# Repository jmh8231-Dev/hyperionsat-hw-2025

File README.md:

# HyperionSAT Flight‑Computer – 하드웨어 (2025)

> **Rev**: 1.0 · **ECAD**: KiCad 9.0.4 · **MCU**: STM32H723VGT6 (550 MHz, DP‑FPU)  
> **역할**: 2차 추진, TVC 제어, 센싱, 통신을 담당하는 하이브리드 비행 컴퓨터

---

<h3>3D Rendering</h3>
<table>
  <tr>
    <td></td>
    <td></td>
  </tr>
  <tr>
    <td align="center"><sub>Top</sub></td>
    <td align="center"><sub>Bottom</sub></td>
  </tr>

  <tr>
    <td></td>
    <td></td>
  </tr>
  <tr>
    <td align="center"><sub>SUB Top</sub></td>
    <td align="center"><sub>SUB Bottom</sub></td>
  </tr>
</table>

---

## 리포지토리 구성 (스냅샷)
```
docs/
└─ images/
   ├─ sch_processor.png
   ├─ sch_sensors.png
   ├─ sch_pmic.png
   ├─ sch_comm.png
   ├─ sch_actuators.png
   └─ sch_additional.png
README.md
```

---

## 1) 시스템 개요

**블록**
- **Processor**: STM32H723VGT6, 12 MHz TCXO, SWD, EEPROM(AT24C08C), RTC(DS3231M), Buzzer/LED, microSD(SDMMC 4‑bit).
- **Flight Sensors**: ICM‑45686(SPI), ICM‑20948(SPI, 1.8 V IO), MS5611(SPI), MMC5983MA(SPI), MAX‑M10S(UART+PPS), VL53L1X(I²C), **CDS‑Top/Bottom**(Bottom=TLV9001 버퍼).
- **Actuators**: TVC 서보 X/Y(12 V), **리니어 솔레노이드**(IRF1404, 어댑터 분리), **낙하산 전개 전자석**(DRV8871DDA).
- **Communications**: LoRa E32‑433T37S(UART + M0/M1/AUX), **Globalstar STX‑3**(UART + EN/RESET), RF 매칭 네트워크.
- **PMIC/Power**: 메인 Li‑Po 3S(셀1/2 버퍼드 ADC), **점화 배터리**(팩 전압 ADC), 3.3 V 스위칭, **INA219** 방전/점화 전류 측정, **AS6221** 온도.

**점화(IGN)**: **1채널** 구성으로 단순화됨.

<h3>Block Diagrams</h3>
<table>
  <tr>
    <td></td>
    <td></td>
    <td></td>
  </tr>
  <tr>
    <td align="center"><sub>OBC</sub></td>
    <td align="center"><sub>Communication</sub></td>
    <td align="center"><sub>Power</sub></td>
  </tr>
</table>

---

## 2) 전기적 인터페이스 (네트 라벨 기준)

### SPI
| Bus | Device | Signals |
|---|---|---|
| SPI‑A | ICM‑45686 | `ICM-45686_SCK/MISO/MOSI/CS`, `ICM-45686_INT` |
| SPI‑B | ICM‑20948, MS5611 | `ICM-20948_SCK/MISO/MOSI/CS`, `IMU2_INT`; `Barometer_SCK/MISO/MOSI/CS` |
| SPI‑C | MMC5983MA | `MMC5983MA_SCK/MISO/MOSI/CS`, `MMC5983MA_INT` |

### I²C (7‑bit)
| Bus | Device | Addr |
|---|---|---|
| RTC | DS3231M | 0x68 |
| EEPROM | AT24C08C | 0x50 *(데이터시트 8‑bit 코드 0xA0)* |
| TEMP | AS6221(Board/PMIC/FET/LoRa) | 0x48 / 0x49 / 0x4B / 0x4A |
| IGN | INA219 | 0x41 |

### UART / 타이밍 / GPIO
| Link | Signals |
|---|---|
| Debug | `Debug_Tx`, `Debug_Rx` |
| LoRa(E32) | `RF_Tx`, `RF_Rx`, `RF_M0`, `RF_M1`, `RF_AUX` |
| STX‑3 | `STX-3_Tx`, `STX-3_Rx`, `STX-3_CTS`, `STX-3_RTS`, `STX-3_EN`, `STX-3_Reset` |
| GPS | `GPS_Tx`, `GPS_Rx`, `GPS_PPS` |
| SDMMC | `SDMMC_D0..D3`, `SDMMC_CLK`, `SDMMC_CMD`, `SDMMC_DET`, `SDMMC_WP` |
| Actuators | `Servo_X`, `Servo_Y`, `Solenoid_Gate`, `DRV8871_A`, `DRV8871_B` |
| Analog | `Main_Cell1_ADC`, `Main_Cell2_ADC`, `IGN_BAT_ADC`, `Back-up_BAT_ADC`, `CDS_Top`, `CDS_Bottom_ADC` |

---

## 3) 회로도 스냅샷

- **Processor**  

- **Flight Sensors**  

- **PMIC / Power**  

- **Communications**  

- **Actuators**  

- **Additional parts (Magnetometer SPI, CDS Bottom 버퍼, LoRa 온도)**  

> **Firmware repo**: [https://github.com/ORG/REPO-FW  ](https://github.com/jmh8231-Dev/hyperionsat-fw-2025)

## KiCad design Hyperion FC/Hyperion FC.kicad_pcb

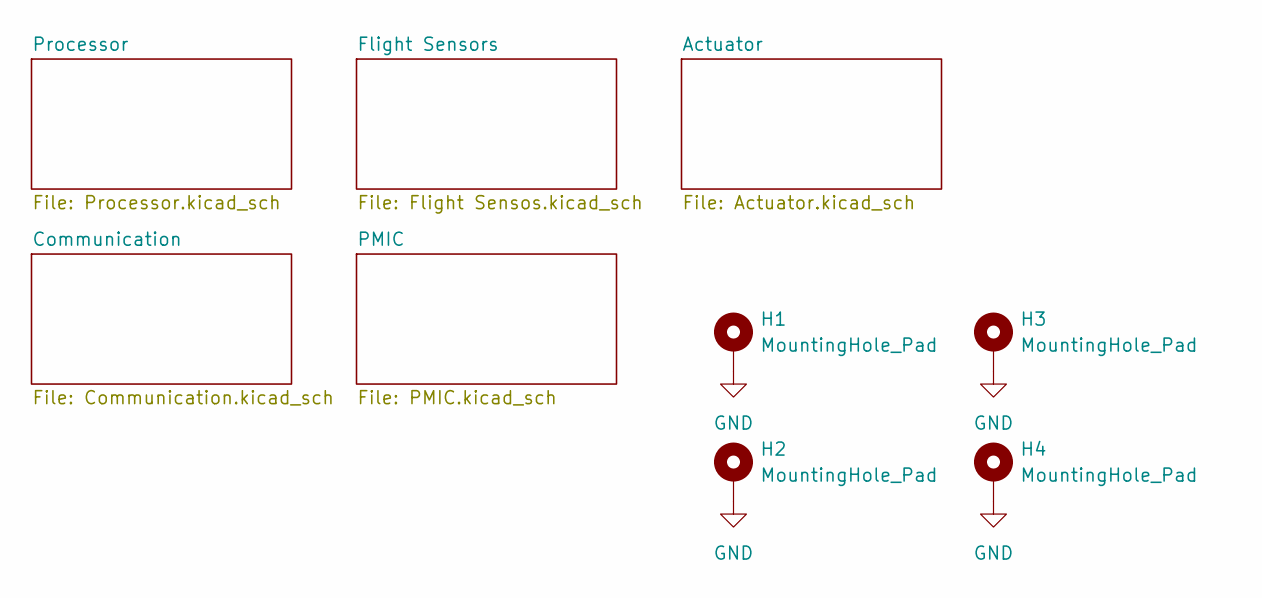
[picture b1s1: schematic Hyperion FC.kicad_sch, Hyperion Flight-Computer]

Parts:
H1, H2, H3, H4: MountingHole_Pad; MountingHole_2.7mm_M2.5_Pad_Via

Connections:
GND: H1.1, H2.1, H3.1, H4.1; also elsewhere on the board

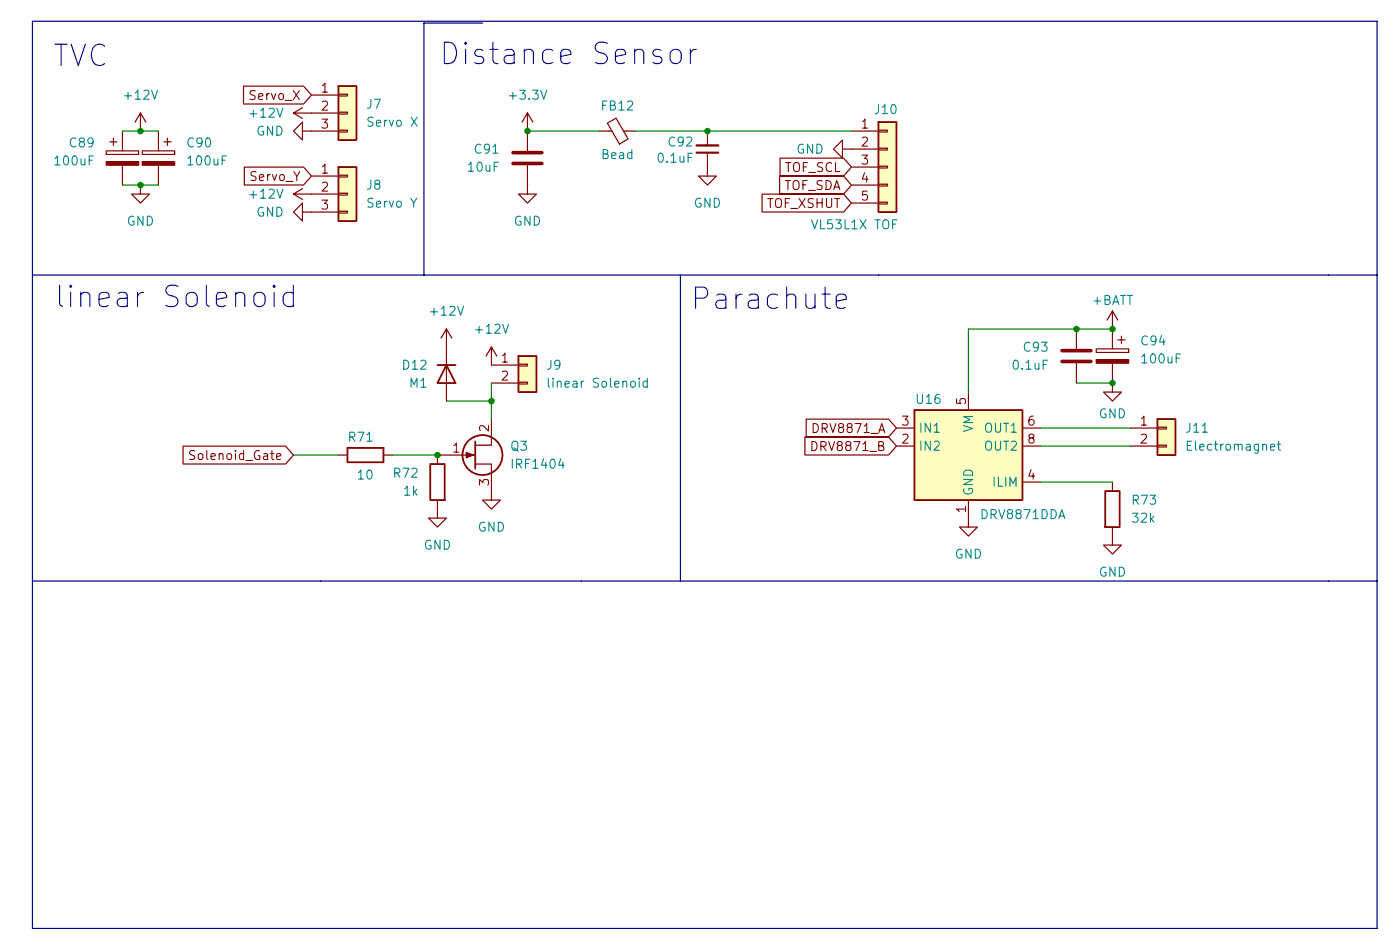
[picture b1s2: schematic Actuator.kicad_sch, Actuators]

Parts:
C89, C90, C94: 100uF; CP_EIA-7343-43_Kemet-X
C91: 10uF; C_0805_2012Metric
C92, C93: 0.1uF; C_0603_1608Metric
D12: M1; D_SMA
FB12: Bead; L_0603_1608Metric
J7: Servo X; JST_VH_B3P-VH_1x03_P3.96mm_Vertical
J8: Servo Y; JST_VH_B3P-VH_1x03_P3.96mm_Vertical
J9: linear Solenoid; JST_VH_B2P-VH_1x02_P3.96mm_Vertical
J10: VL53L1X TOF; SAMTEC_T1M-05-F-SH-L
J11: Electromagnet; JST_VH_B2P-VH_1x02_P3.96mm_Vertical
Q3: IRF1404; TO-263-2
R71: 10; R_0603_1608Metric
R72: 1k; R_0603_1608Metric
R73: 32k; R_0603_1608Metric
U16: DRV8871DDA; Texas_HTSOP-8-1EP_3.9x4.9mm_P1.27mm_EP2.95x4.9mm_Mask2.4x3.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

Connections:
+3.3V: C91.1, FB12.2; also elsewhere on the board
+12V: C89.1, C90.1, D12.1 (K), J7.2, J8.2, J9.1; also elsewhere on the board
+BATT: C93.1, C94.1, U16.5 (VM); also elsewhere on the board
DRV8871_A: U16.3 (IN1); also elsewhere on the board
DRV8871_B: U16.2 (IN2); also elsewhere on the board
GND: C89.2, C90.2, C91.2, C92.1, C93.2, C94.2, J7.3, J8.3, J10.2, Q3.3 (S), R72.2, R73.2, U16.1 (GND), U16.7 (GND), U16.9 (GND); also elsewhere on the board
I2C4_SCL: J10.3; also elsewhere on the board
I2C4_SDA: J10.4; also elsewhere on the board
unnamed: D12.2 (A), J9.2, Q3.2 (D)
unnamed: C92.2, FB12.1, J10.1
unnamed: J11.1, U16.6 (OUT1)
unnamed: J11.2, U16.8 (OUT2)
unnamed: Q3.1 (G), R71.2, R72.1
unnamed: R73.1, U16.4 (ILIM)
Servo_X: J7.1; also elsewhere on the board
Servo_Y: J8.1; also elsewhere on the board
Solenoid_Gate: R71.1; also elsewhere on the board
TOF_XSHUT: J10.5; also elsewhere on the board

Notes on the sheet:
linear Solenoid
Parachute
TVC
Distance Sensor

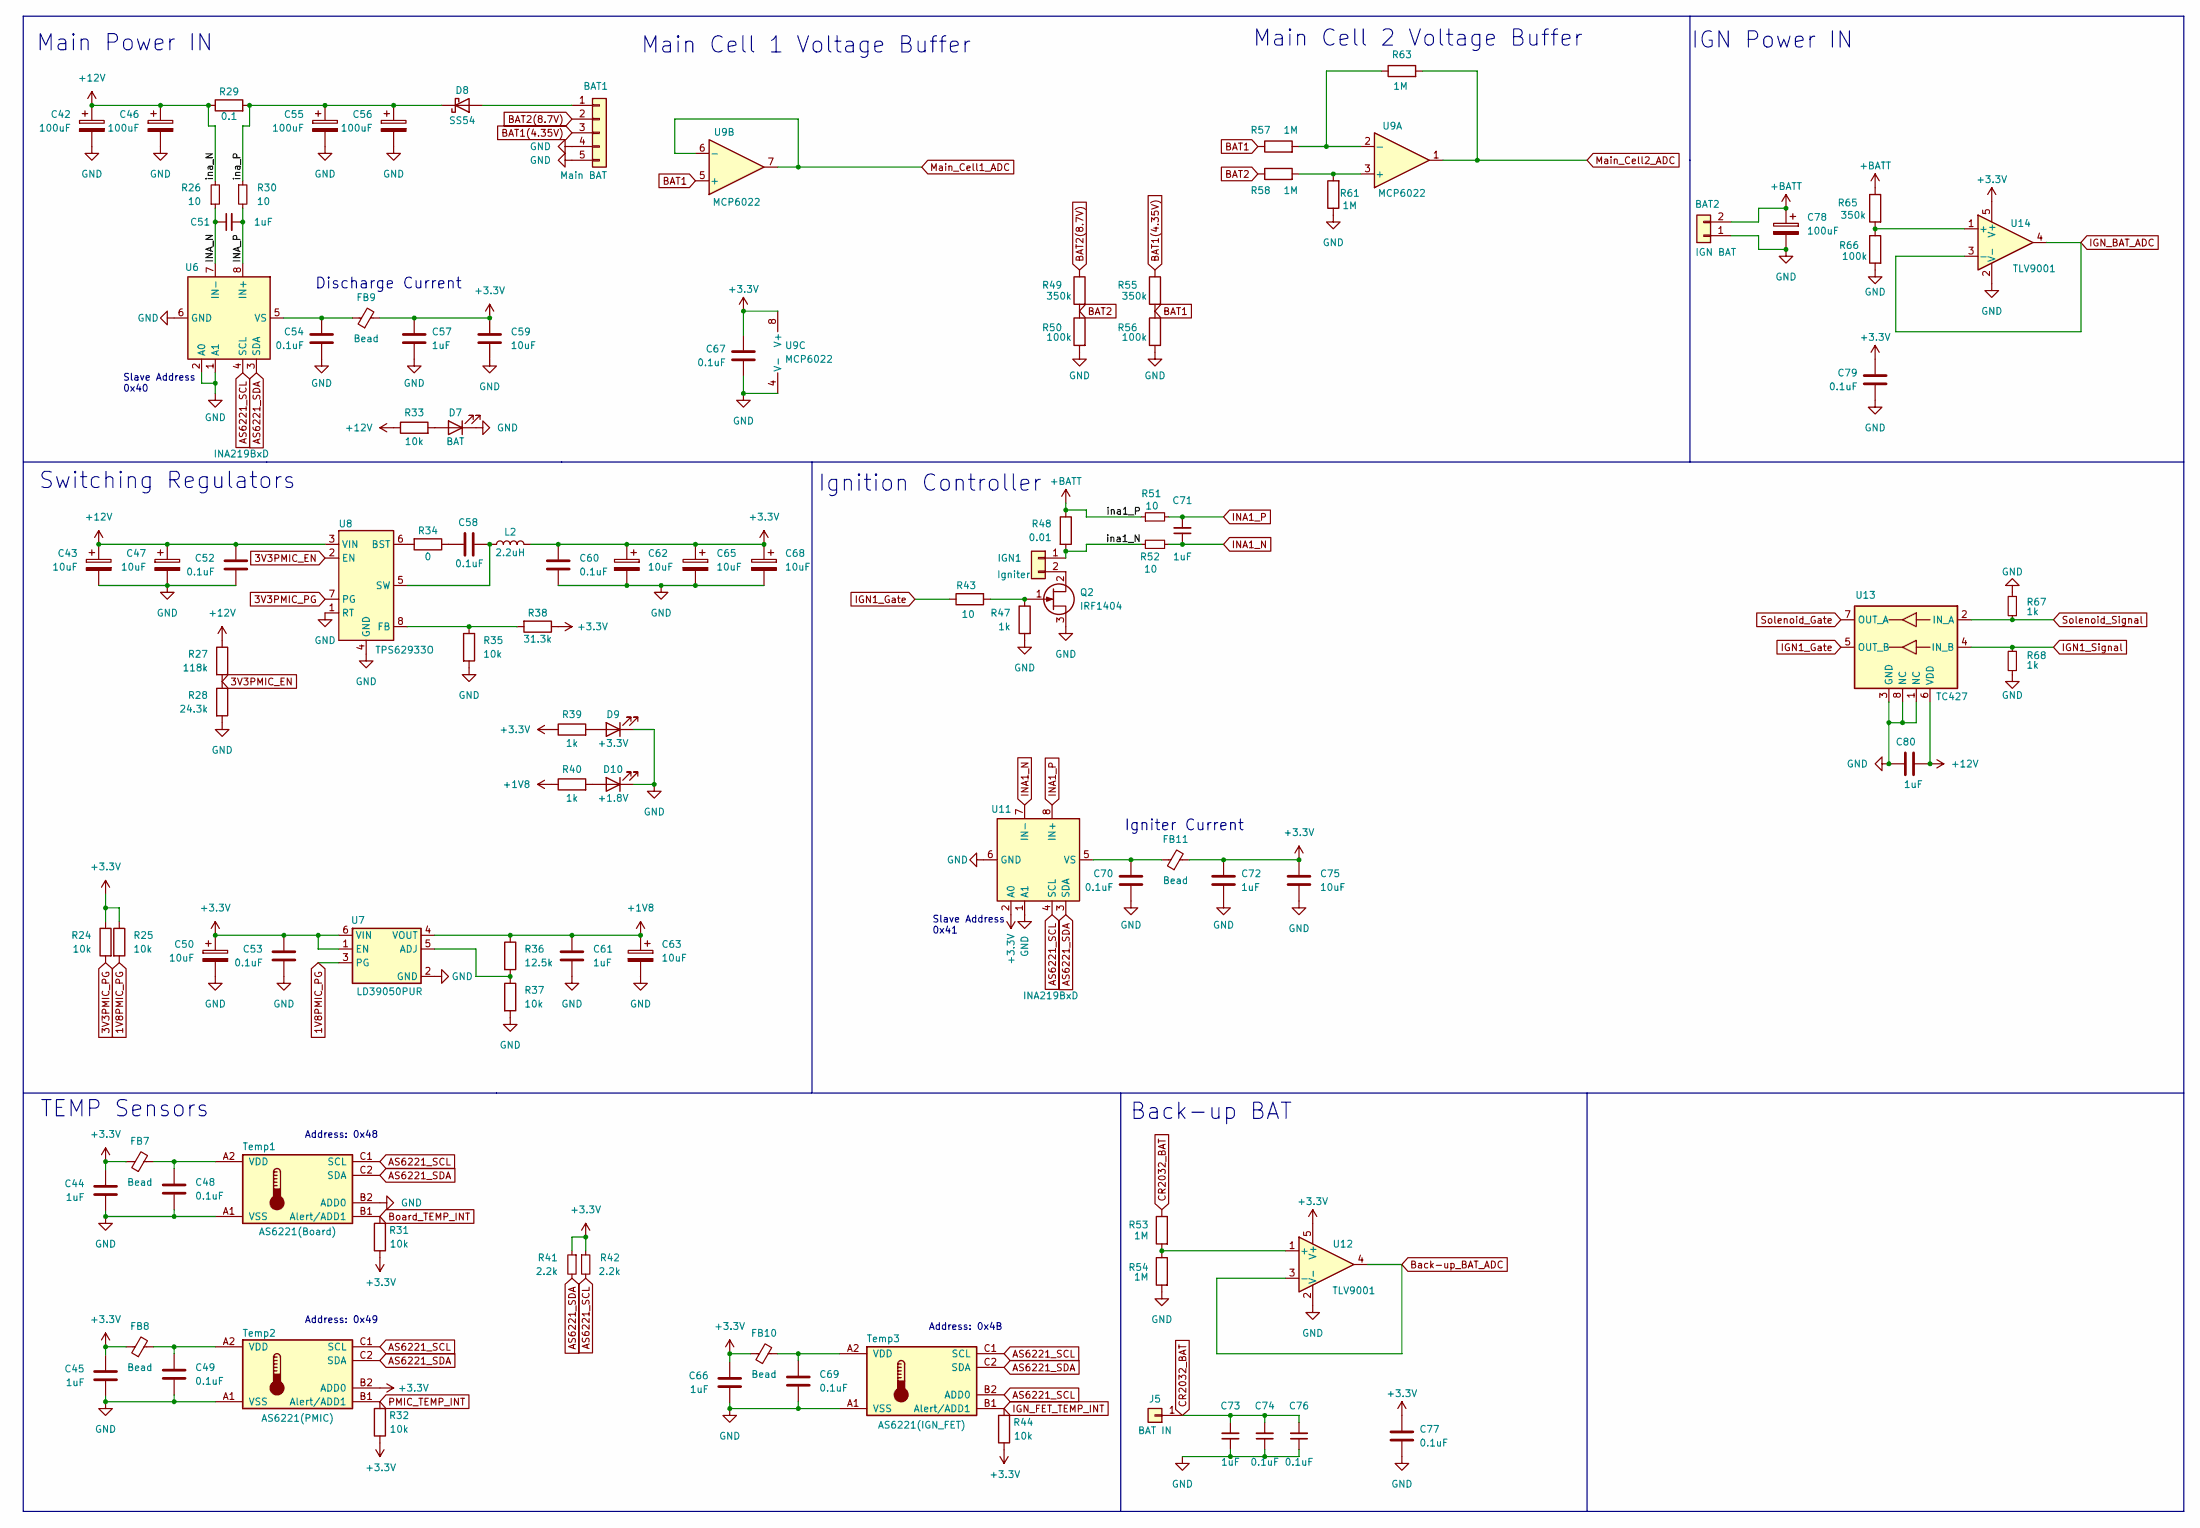
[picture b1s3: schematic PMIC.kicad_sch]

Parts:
BAT1: Main BAT; SAMTEC_T1M-05-F-SH-L
BAT2: IGN BAT; AMASS_XT30U-M_1x02_P5.0mm_Vertical
C42, C46, C55, C56, C78: 100uF; CP_EIA-7343-43_Kemet-X
C43, C47, C50, C59, C62, C63, C65, C68, C75: 10uF; C_0805_2012Metric
C44, C45, C51, C57, C61, C66, C71, C72, C73, C80: 1uF; C_0603_1608Metric
C48, C49, C52, C53, C54, C58, C60, C67, C69, C70, C74, C76, C77, C79: 0.1uF; C_0603_1608Metric
D7: BAT; LED_0805_2012Metric
D8: SS54; D_SMA
D9: +3.3V; LED_0805_2012Metric
D10: +1.8V; LED_0805_2012Metric
FB7, FB8, FB9, FB10, FB11: Bead; L_0603_1608Metric
IGN1: Igniter; JST_VH_B2P-VH_1x02_P3.96mm_Vertical
J5: BAT IN; PinHeader_1x01_P2.54mm_Vertical
L2: 2.2uH; L_Coilcraft_XAL6030-XXX
Q2: IRF1404; TO-263-2
R24, R25, R31, R32, R33, R35, R37, R44: 10k; R_0603_1608Metric
R26, R30, R43, R51, R52: 10; R_0603_1608Metric
R27: 118k; R_0603_1608Metric
R28: 24.3k; R_0603_1608Metric
R29: 0.1; R_2816_7142Metric
R34: 0; R_0603_1608Metric
R36: 12.5k; R_0603_1608Metric
R38: 31.3k; R_0603_1608Metric
R39, R40, R47, R67, R68: 1k; R_0603_1608Metric
R41, R42: 2.2k; R_0603_1608Metric
R48: 0.01; R_2816_7142Metric
R49, R55, R65: 350k; R_0603_1608Metric
R50, R56, R66: 100k; R_0603_1608Metric
R53, R54, R57, R58, R61, R63: 1M; R_0603_1608Metric
Temp1: AS6221(Board); WLCSP-6_1.4x1.0mm_P0.4mm
Temp2: AS6221(PMIC); WLCSP-6_1.4x1.0mm_P0.4mm
Temp3: AS6221(IGN_FET); WLCSP-6_1.4x1.0mm_P0.4mm
U6, U11: INA219BxD; SOIC-8_3.9x4.9mm_P1.27mm
U7: LD39050PUR; DFN-6-1EP_3x3mm_P0.95mm_EP1.7x2.6mm
U8: TPS62933O; SOT-583-8
U9: MCP6022; SOIC-8_3.9x4.9mm_P1.27mm
U12, U14: TLV9001; SOT-353_SC-70-5
U13: TC427; SOIC-8_3.9x4.9mm_P1.27mm

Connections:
1V8PMIC_PG: R25.2, U7.3 (PG); also elsewhere on the board
3V3PMIC_EN: R27.2, R28.1, U8.2 (EN)
3V3PMIC_PG: R24.2, U8.7 (PG); also elsewhere on the board
+1V8: C61.1, C63.1, R36.1, R40.1, U7.4 (VOUT); also elsewhere on the board
+3.3V: C44.2, C45.2, C50.1, C53.1, C57.1, C59.1, C60.1, C62.1, C65.1, C66.2, C67.2, C68.1, C72.1, C75.1, C77.2, C79.2, FB7.1, FB8.1, FB9.2, FB10.1, FB11.2, L2.2, R24.1, R25.1, R31.1, R32.1, R38.1, R39.1, R41.1, R42.1, R44.1, Temp2.B2 (ADD0), U7.1 (EN), U7.6 (VIN), U9.8 (V+), U11.2 (A0), U12.5 (V+), U14.5 (V+); also elsewhere on the board
+12V: C42.1, C43.1, C46.1, C47.1, C52.1, C80.2, R26.2, R27.1, R29.1, R33.1, U8.3 (VIN), U13.6 (VDD); also elsewhere on the board
+BATT: BAT2.2, C78.1, R48.1, R51.1, R65.1; also elsewhere on the board
/PMIC/INA_N: C51.1, R26.1, U6.7 (IN-)
/PMIC/INA_P: C51.2, R30.2, U6.8 (IN+)
/PMIC/ina1_N: IGN1.1, R48.2, R52.2
/PMIC/ina_P: C55.1, C56.1, D8.1 (K), R29.2, R30.1
AS6221_SCL: R42.2, Temp1.C1 (SCL), Temp2.C1 (SCL), Temp3.B2 (ADD0), Temp3.C1 (SCL), U6.4 (SCL), U11.4 (SCL); also elsewhere on the board
AS6221_SDA: R41.2, Temp1.C2 (SDA), Temp2.C2 (SDA), Temp3.C2 (SDA), U6.3 (SDA), U11.3 (SDA); also elsewhere on the board
BAT1: R55.2, R56.1, R57.1, U9.5 (+)
BAT1(4.35V): BAT1.3, R55.1
BAT2: R49.2, R50.1, R58.1
BAT2(8.7V): BAT1.2, R49.1
Back-up_BAT_ADC: U12.3 (-), U12.4; also elsewhere on the board
Board_TEMP_INT: R31.2, Temp1.B1 (Alert/ADD1); also elsewhere on the board
CR2032_BAT: C73.2, C74.2, C76.2, J5.1, R53.1; also elsewhere on the board
GND: BAT1.4, BAT1.5, BAT2.1, C42.2, C43.2, C44.1, C45.1, C46.2, C47.2, C48.2, C49.2, C50.2, C52.2, C53.2, C54.2, C55.2, C56.2, C57.2, C59.2, C60.2, C61.2, C62.2, C63.2, C65.2, C66.1, C67.1, C68.2, C69.2, C70.2, C72.2, C73.1, C74.1, C75.2, C76.1, C77.1, C78.2, C79.1, C80.1, D7.1 (K), D9.1 (K), D10.1 (K), Q2.3 (S), R28.2, R35.2, R37.2, R47.2, R50.2, R54.2, R56.2, R61.1, R66.2, R67.1, R68.1, Temp1.A1 (VSS), Temp1.B2 (ADD0), Temp2.A1 (VSS), Temp3.A1 (VSS), U6.1 (A1), U6.2 (A0), U6.6 (GND), U7.2 (GND), U7.7 (EP), U8.1 (RT), U8.4 (GND), U9.4 (V-), U11.1 (A1), U11.6 (GND), U12.2 (V-), U13.1 (NC), U13.3 (GND), U13.8 (NC), U14.2 (V-); also elsewhere on the board
IGN1_Gate: R43.1, U13.5 (OUT_B)
IGN1_Signal: R68.2, U13.4 (IN_B); also elsewhere on the board
IGN_BAT_ADC: U14.3 (-), U14.4; also elsewhere on the board
IGN_FET_TEMP_INT: R44.2, Temp3.B1 (Alert/ADD1); also elsewhere on the board
INA1_N: C71.1, R52.1, U11.7 (IN-)
INA1_P: C71.2, R51.2, U11.8 (IN+)
Main_Cell1_ADC: U9.6 (-), U9.7; also elsewhere on the board
Main_Cell2_ADC: R63.2, U9.1; also elsewhere on the board
unnamed: BAT1.1, D8.2 (A)
unnamed: C58.1, R34.1
unnamed: D7.2 (A), R33.2
unnamed: D9.2 (A), R39.2
unnamed: D10.2 (A), R40.2
unnamed: IGN1.2, Q2.2 (D)
unnamed: Q2.1 (G), R43.2, R47.1
unnamed: C48.1, FB7.2, Temp1.A2 (VDD)
unnamed: C49.1, FB8.2, Temp2.A2 (VDD)
unnamed: C69.1, FB10.2, Temp3.A2 (VDD)
unnamed: C54.1, FB9.1, U6.5 (VS)
unnamed: R36.2, R37.1, U7.5 (ADJ)
unnamed: R34.2, U8.6 (BST)
unnamed: R35.1, R38.2, U8.8 (FB)
unnamed: C58.2, L2.1, U8.5 (SW)
unnamed: R58.2, R61.2, U9.3 (+)
unnamed: R57.2, R63.1, U9.2 (-)
unnamed: C70.1, FB11.1, U11.5 (VS)
unnamed: R53.2, R54.1, U12.1 (+)
unnamed: R65.2, R66.1, U14.1 (+)
PMIC_TEMP_INT: R32.2, Temp2.B1 (Alert/ADD1); also elsewhere on the board
Solenoid_Gate: U13.7 (OUT_A); also elsewhere on the board
Solenoid_Signal: R67.2, U13.2 (IN_A); also elsewhere on the board

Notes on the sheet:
Address: 0x48
Switching Regulators
TEMP Sensors
Back-up BAT
Address: 0x4B
Main Power IN
Slave Address 0x41
Address: 0x49
Slave Address 0x40
Main Cell 2 Voltage Buffer
Igniter Current
Discharge Current
IGN Power IN
Main Cell 1 Voltage Buffer
Ignition Controller

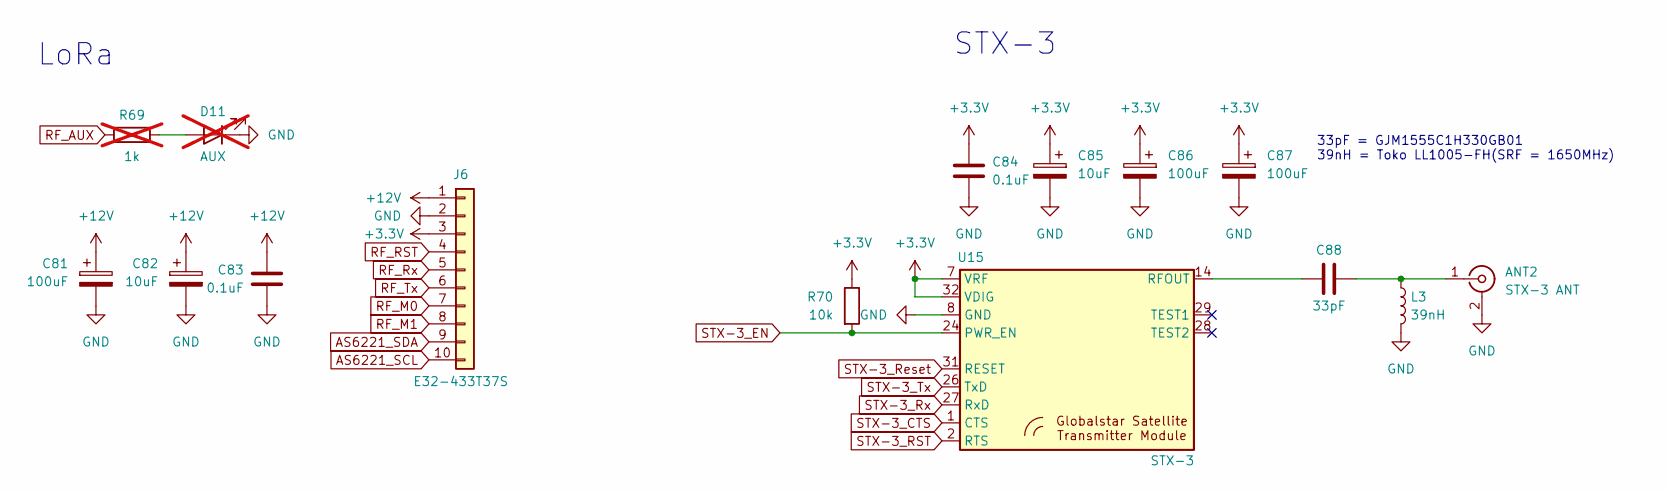
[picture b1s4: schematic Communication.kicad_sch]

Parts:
ANT2: STX-3 ANT; MMCX_Molex_73415-1471_Vertical
C81, C86, C87: 100uF; CP_EIA-7343-43_Kemet-X
C82, C85: 10uF; C_0805_2012Metric
C83, C84: 0.1uF; C_0603_1608Metric
C88: 33pF; C_0402_1005Metric
D11: AUX; LED_0805_2012Metric; not fitted
J6: E32-433T37S; SAMTEC_T1M-10-F-SH-L-K
L3: 39nH; L_0402_1005Metric
R69: 1k; R_0603_1608Metric; not fitted
R70: 10k; R_0603_1608Metric
U15: STX-3

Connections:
+3.3V: C84.1, C85.1, C86.1, C87.1, J6.3, R70.1, U15.7 (VRF), U15.32 (VDIG); also elsewhere on the board
+12V: C81.1, C82.1, C83.1, J6.1; also elsewhere on the board
AS6221_SCL: J6.10; also elsewhere on the board
AS6221_SDA: J6.9; also elsewhere on the board
GND: ANT2.2 (Ext), C81.2, C82.2, C83.2, C84.2, C85.2, C86.2, C87.2, D11.1 (K), J6.2, L3.2, U15.8 (GND), U15.9 (GND), U15.10 (GND), U15.11 (GND), U15.12 (GND), U15.13 (GND), U15.15 (GND), U15.16 (GND), U15.17 (GND), U15.18 (GND), U15.19 (GND), U15.20 (GND); also elsewhere on the board
unnamed: ANT2.1 (In), C88.2, L3.1
unnamed: D11.2 (A), R69.2
unnamed: C88.1, U15.14 (RFOUT)
RF_M0: J6.7; also elsewhere on the board
RF_M1: J6.8; also elsewhere on the board
RF_RST: J6.4; also elsewhere on the board
RF_Rx: J6.5; also elsewhere on the board
RF_Tx: J6.6; also elsewhere on the board
STX-3_CTS: U15.1 (CTS); also elsewhere on the board
STX-3_EN: R70.2, U15.24 (PWR_EN); also elsewhere on the board
STX-3_RST: U15.2 (RTS); also elsewhere on the board
STX-3_Reset: U15.31 (RESET); also elsewhere on the board
STX-3_Rx: U15.27 (RxD); also elsewhere on the board
STX-3_Tx: U15.26 (TxD); also elsewhere on the board

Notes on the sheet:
33pF = GJM1555C1H330GB01 39nH = Toko LL1005-FH(SRF = 1650MHz)
STX-3
LoRa

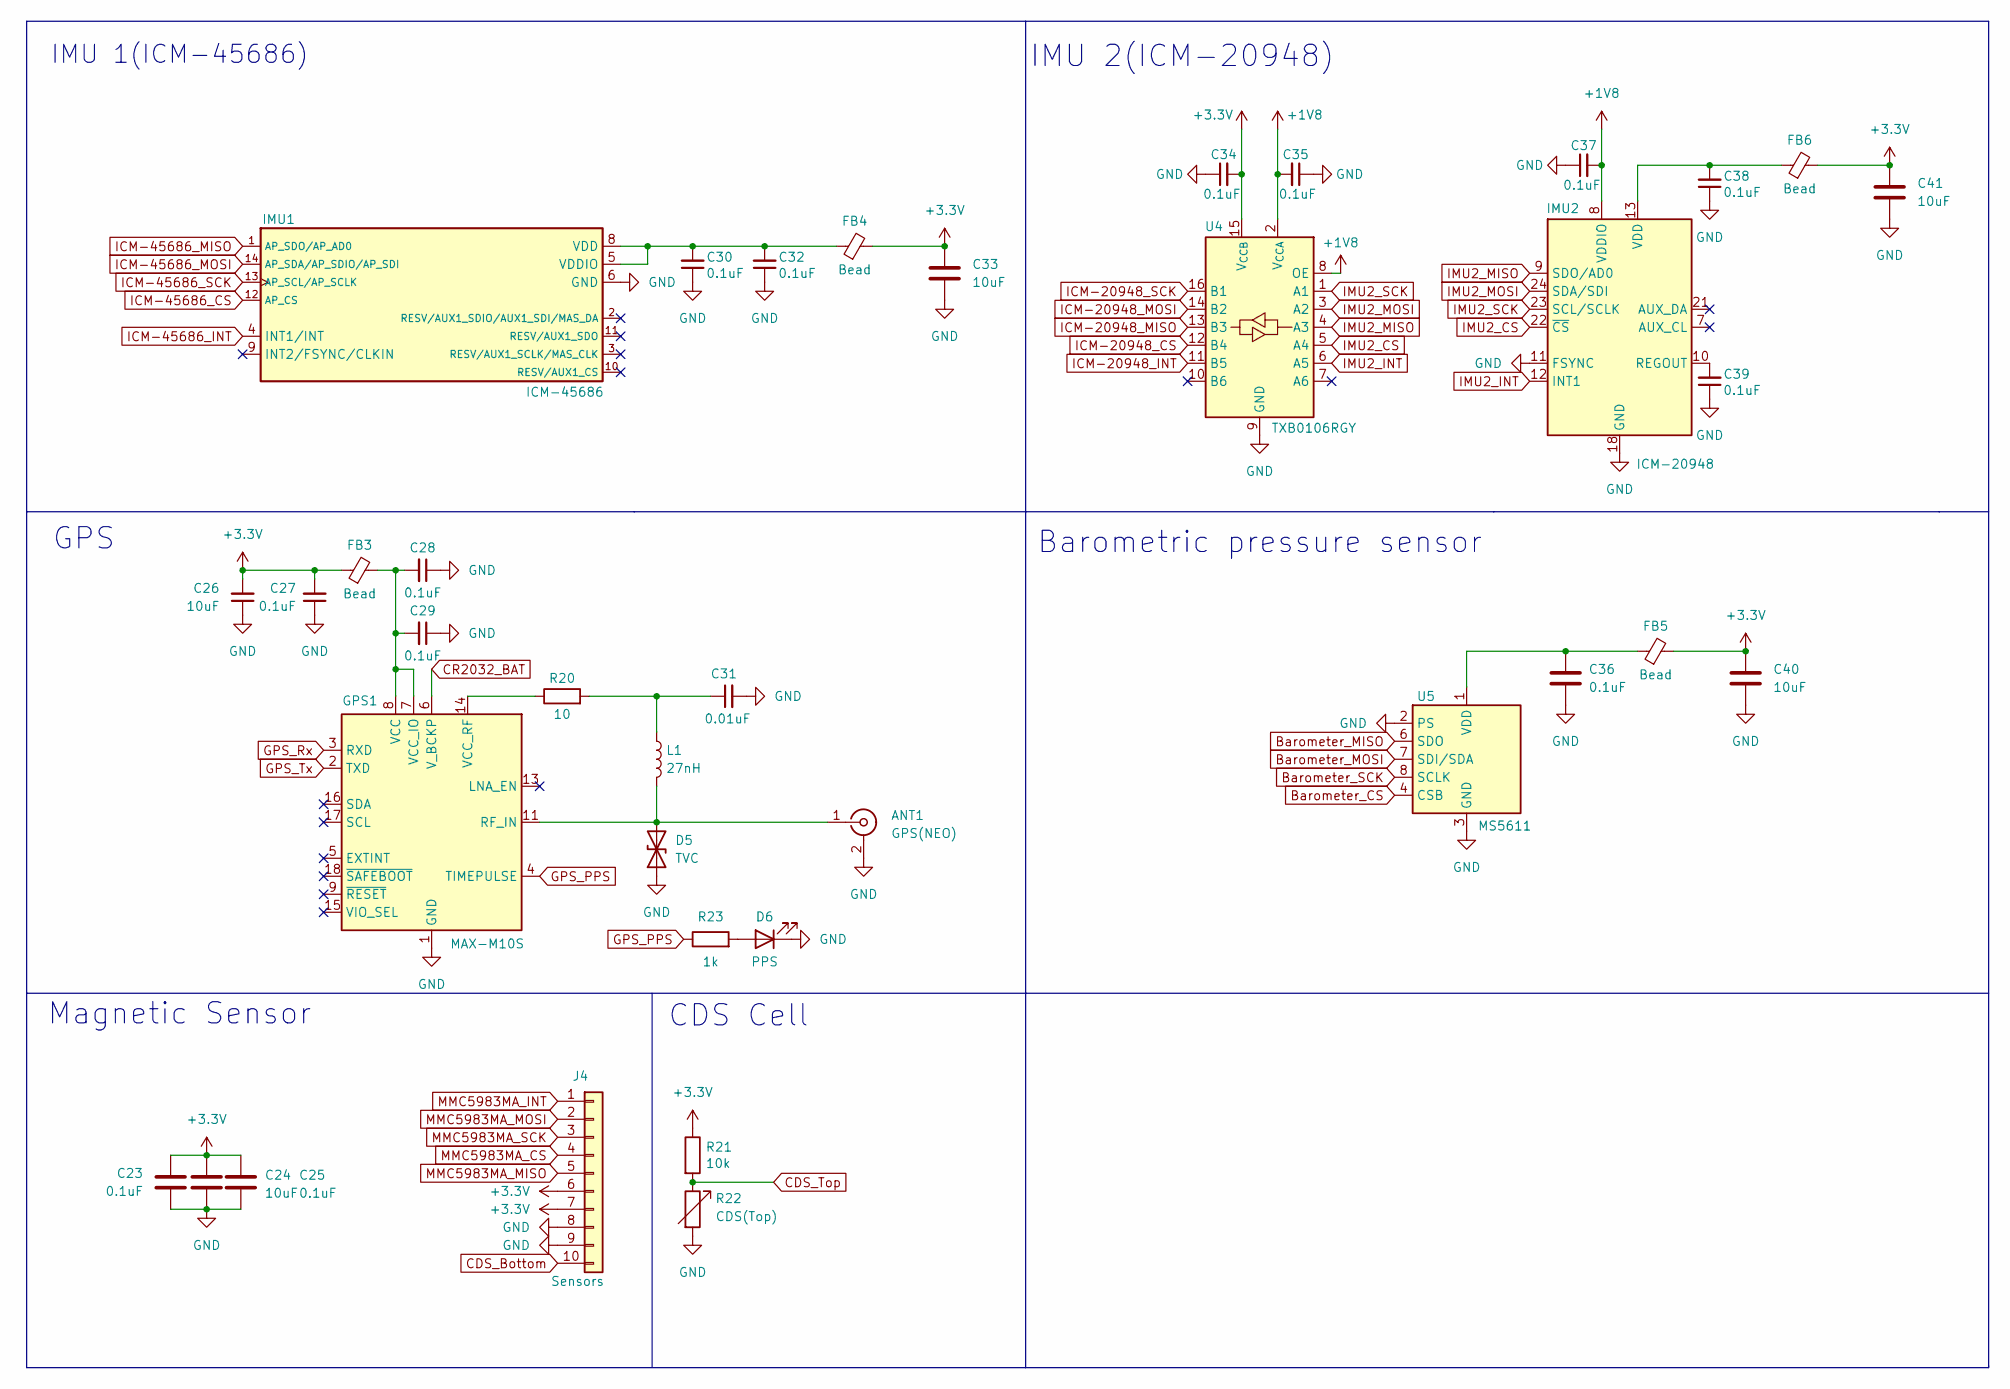
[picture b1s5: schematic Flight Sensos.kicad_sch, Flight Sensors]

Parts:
ANT1: GPS(NEO); SMA_Amphenol_132134-11_Vertical
C23, C25, C27, C28, C29, C30, C32, C34, C35, C36, C37, C38, C39: 0.1uF; C_0603_1608Metric
C24, C26, C33, C40, C41: 10uF; C_0805_2012Metric
C31: 0.01uF; C_0603_1608Metric
D5: TVC; D_0402_1005Metric
D6: PPS; LED_0805_2012Metric
FB3, FB4, FB5, FB6: Bead; L_0603_1608Metric
GPS1: MAX-M10S; ublox_MAX
IMU1: ICM-45686; IC_ICM-45686
IMU2: ICM-20948; InvenSense_QFN-24_3x3mm_P0.4mm
J4: Sensors; SAMTEC_T1M-10-F-SH-L-K
L1: 27nH; L_0805_2012Metric
R20: 10; R_0603_1608Metric
R21: 10k; R_0603_1608Metric
R22: CDS(Top); R_LDR_5.0x4.1mm_P3mm_Vertical
R23: 1k; R_0603_1608Metric
U4: TXB0106RGY; Texas_RGY_R-PVQFN-N16_EP2.05x2.55mm
U5: MS5611; LGA-8_3x5mm_P1.25mm

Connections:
+1V8: C35.2, C37.2, IMU2.8 (VDDIO), U4.2 (V_{CCA}), U4.8 (OE); also elsewhere on the board
+3.3V: C23.1, C24.1, C25.1, C26.2, C27.2, C33.1, C34.2, C40.1, C41.1, FB3.1, FB4.2, FB5.2, FB6.2, J4.6, J4.7, R21.1, U4.15 (V_{CCB}); also elsewhere on the board
Barometer_CS: U5.4 (CSB), U5.5 (CSB); also elsewhere on the board
Barometer_MISO: U5.6 (SDO); also elsewhere on the board
Barometer_MOSI: U5.7 (SDI/SDA); also elsewhere on the board
Barometer_SCK: U5.8 (SCLK); also elsewhere on the board
CDS_Bottom: J4.10; also elsewhere on the board
CDS_Top: R21.2, R22.1; also elsewhere on the board
CR2032_BAT: GPS1.6 (V_BCKP); also elsewhere on the board
GND: ANT1.2 (Ext), C23.2, C24.2, C25.2, C26.1, C27.1, C28.1, C29.1, C30.1, C31.2, C32.1, C33.2, C34.1, C35.1, C36.2, C37.1, C38.1, C39.1, C40.2, C41.2, D5.1 (A1), D6.1 (K), GPS1.1 (GND), GPS1.10 (GND), GPS1.12 (GND), IMU1.6 (GND), IMU1.7 (RESV), IMU2.11 (FSYNC), IMU2.18 (GND), IMU2.20 (GND), J4.8, J4.9, R22.2, U4.9 (GND), U4.17 (GND), U5.2 (PS), U5.3 (GND); also elsewhere on the board
GPS_PPS: GPS1.4 (TIMEPULSE), R23.1
GPS_Rx: GPS1.3 (RXD); also elsewhere on the board
GPS_Tx: GPS1.2 (TXD); also elsewhere on the board
ICM-20948_CS: U4.12 (B4); also elsewhere on the board
ICM-20948_INT: U4.11 (B5); also elsewhere on the board
ICM-20948_MISO: U4.13 (B3); also elsewhere on the board
ICM-20948_MOSI: U4.14 (B2); also elsewhere on the board
ICM-20948_SCK: U4.16 (B1); also elsewhere on the board
ICM-45686_CS: IMU1.12 (AP_CS); also elsewhere on the board
ICM-45686_INT: IMU1.4 (INT1/INT); also elsewhere on the board
ICM-45686_MISO: IMU1.1 (AP_SDO/AP_AD0); also elsewhere on the board
ICM-45686_MOSI: IMU1.14 (AP_SDA/AP_SDIO/AP_SDI); also elsewhere on the board
ICM-45686_SCK: IMU1.13 (AP_SCL/AP_SCLK); also elsewhere on the board
IMU2_CS: IMU2.22 (~CS), U4.5 (A4)
IMU2_INT: IMU2.12 (INT1), U4.6 (A5)
IMU2_MISO: IMU2.9 (SDO/AD0), U4.4 (A3)
IMU2_MOSI: IMU2.24 (SDA/SDI), U4.3 (A2)
IMU2_SCK: IMU2.23 (SCL/SCLK), U4.1 (A1)
MMC5983MA_CS: J4.4; also elsewhere on the board
MMC5983MA_INT: J4.1; also elsewhere on the board
MMC5983MA_MISO: J4.5; also elsewhere on the board
MMC5983MA_MOSI: J4.2; also elsewhere on the board
MMC5983MA_SCK: J4.3; also elsewhere on the board
unnamed: ANT1.1 (In), D5.2 (A2), GPS1.11 (RF_IN), L1.2
unnamed: C31.1, L1.1, R20.2
unnamed: D6.2 (A), R23.2
unnamed: C28.2, C29.2, FB3.2, GPS1.7 (VCC_IO), GPS1.8 (VCC)
unnamed: GPS1.14 (VCC_RF), R20.1
unnamed: C30.2, C32.2, FB4.1, IMU1.5 (VDDIO), IMU1.8 (VDD)
unnamed: C39.2, IMU2.10 (REGOUT)
unnamed: C38.2, FB6.1, IMU2.13 (VDD)
unnamed: C36.1, FB5.1, U5.1 (VDD)

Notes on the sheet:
GPS
IMU 2(ICM-20948)
IMU 1(ICM-45686)
CDS Cell
Magnetic Sensor
Barometric pressure sensor
